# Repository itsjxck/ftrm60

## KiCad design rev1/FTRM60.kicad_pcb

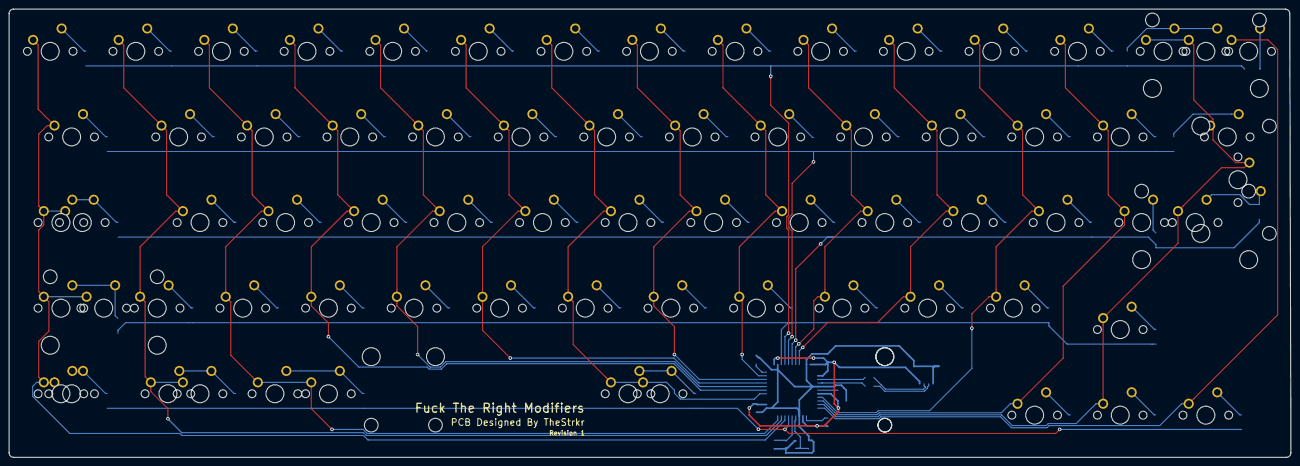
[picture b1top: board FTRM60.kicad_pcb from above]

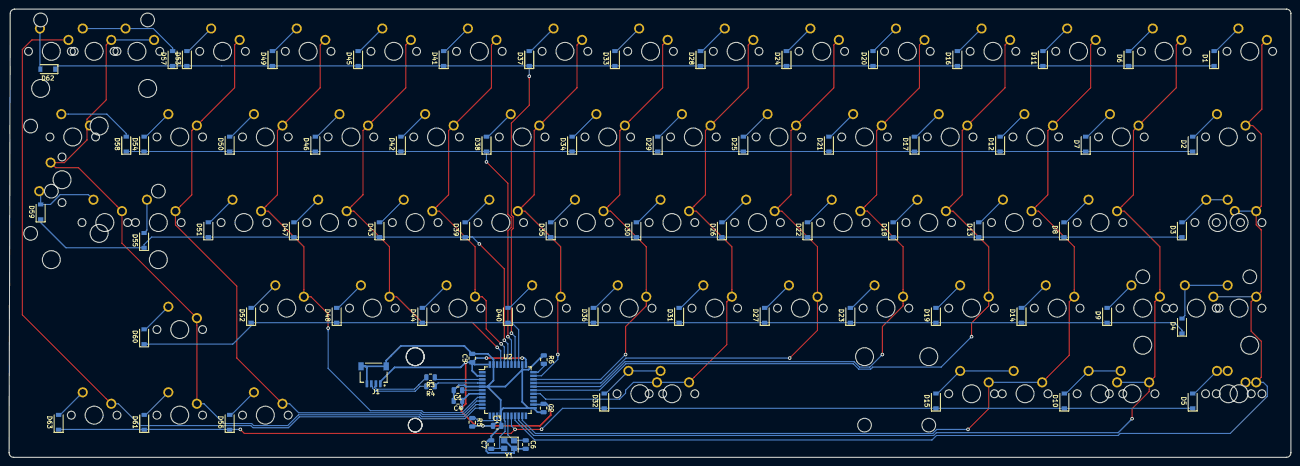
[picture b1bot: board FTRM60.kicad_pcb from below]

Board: 2 copper layers, 285.2 x 99.8 mm, 148 parts (77 on the bottom side), 94 nets.

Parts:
C1: 1uF; C_0805_2012Metric
C2, C3, C4: 0.1uF; C_0805_2012Metric
C5: 10uF; C_0805_2012Metric
C6, C7: 22pF; C_0805_2012Metric
D1, D2, D3, D4, D5, D6, D7, D8, D9, D10, D11, D12, D13, D14, D15, D16, D17, D18, D19, D20, D21, D22, D23, D24, D25, D26, D27, D28, D29, D30, D31, D32, D33, D34, D35, D36, D37, D38, D39, D40, D41, D42, D43, D44, D45, D46, D47, D48, D49, D50, D51, D52, D53, D54, D55, D56, D57, D58, D59, D60, D61, D62, D63: SOD-123; D_SOD-123
J1: SM04B-SRSS-TB(LF)(SN); JST_SM04B-SRSS-TB(LF)(SN)
MX1: K_ESC; MXOnly-1U-NoLED
MX2: K_TAB; MXOnly-1.5U-NoLED
MX3: K_CAPS_S; MXOnly-1.25U-NoLED
MX4: K_CAPS; MXOnly-1.75U-NoLED
MX5: K_LSHIFT_1.25U; MXOnly-1.25U-NoLED
MX6: K_LSHIFT_2.25U; MXOnly-2.25U-NoLED
MX7: K_LCTRL_1.25U; MXOnly-1.25U-NoLED
MX8: K_LCTRL_1.5U; MXOnly-1.5U-NoLED
MX9: K_1; MXOnly-1U-NoLED
MX10: K_Q; MXOnly-1U-NoLED
MX11: K_A; MXOnly-1U-NoLED
MX12: K_NUBS; MXOnly-1U-NoLED
MX13: K_LGUI_1.25U; MXOnly-1.25U-NoLED
MX14: K_LGUI_1.5U; MXOnly-1.5U-NoLED
MX15: K_2; MXOnly-1U-NoLED
MX16: K_W; MXOnly-1U-NoLED
MX17: K_S; MXOnly-1U-NoLED
MX18: K_Z; MXOnly-1U-NoLED
MX19: K_LALT_1.25U; MXOnly-1.25U-NoLED
MX20: K_LALT_1.5U; MXOnly-1.5U-NoLED
MX21: K_3; MXOnly-1U-NoLED
MX22: K_E; MXOnly-1U-NoLED
MX23: K_D; MXOnly-1U-NoLED
MX24: K_X; MXOnly-1U-NoLED
MX25: K_4; MXOnly-1U-NoLED
MX26: K_R; MXOnly-1U-NoLED
MX27: K_F; MXOnly-1U-NoLED
MX28: K_C; MXOnly-1U-NoLED
MX29: K_5; MXOnly-1U-NoLED
MX30: K_T; MXOnly-1U-NoLED
MX31: K_G; MXOnly-1U-NoLED
MX32: K_V; MXOnly-1U-NoLED
MX33: K_6; MXOnly-1U-NoLED
MX34: K_Y; MXOnly-1U-NoLED
MX35: K_H; MXOnly-1U-NoLED
MX36: K_B; MXOnly-1U-NoLED
MX37: K_SPC_7U; MXOnly-7U-ReversedStabilizers-NoLED
MX38: K_SPC_6.25U; MXOnly-6.25U-ReversedStabilizers-NoLED
MX39: K_7; MXOnly-1U-NoLED
MX40: K_U; MXOnly-1U-NoLED
MX41: K_J; MXOnly-1U-NoLED
MX42: K_N; MXOnly-1U-NoLED
MX43: K_8; MXOnly-1U-NoLED
MX44: K_I; MXOnly-1U-NoLED
MX45: K_K; MXOnly-1U-NoLED
MX46: K_M; MXOnly-1U-NoLED
MX47: K_9; MXOnly-1U-NoLED
MX48: K_O; MXOnly-1U-NoLED
MX49: K_L; MXOnly-1U-NoLED
MX50: K_COMM; MXOnly-1U-NoLED
MX51: K_0; MXOnly-1U-NoLED
MX52: K_P; MXOnly-1U-NoLED
MX53: K_SCLN; MXOnly-1U-NoLED
MX54: K_DOT; MXOnly-1U-NoLED
MX55: K_MINS; MXOnly-1U-NoLED
MX56: K_LBRC; MXOnly-1U-NoLED
MX57: K_QUOT; MXOnly-1U-NoLED
MX58: K_SLSH; MXOnly-1U-NoLED
MX59: K_EQL; MXOnly-1U-NoLED
MX60: K_RBRC; MXOnly-1U-NoLED
MX61: K_NUHS; MXOnly-1U-NoLED
MX62: K_LEFT; MXOnly-1U-NoLED
MX63: K_BSPC_S1; MXOnly-1U-NoLED
MX64: K_BSPC; MXOnly-2U-NoLED
MX65: K_BSLS; MXOnly-1.5U-NoLED
MX66: K_ENT_ANSI; MXOnly-2.25U-NoLED
MX67: K_ENT_ISO; MXOnly-ISO-ROTATED-ReversedStabilizers-NoLED
MX68: K_UP; MXOnly-1U-NoLED
MX69: K_DOWN; MXOnly-1U-NoLED
MX70: K_BSPC_S2; MXOnly-1U-NoLED
MX71: K_RIGHT; MXOnly-1U-NoLED
R3, R4: 22; R_0805_2012Metric
R5, R6: 10k; R_0805_2012Metric
U2: ATmega32U4-AU; TQFP-44_10x10mm_P0.8mm
Y1: 16MHz; Crystal_SMD_3225-4Pin_3.2x2.5mm

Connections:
+5V: C2.1, C3.1, C4.1, C5.1, J1.1, R5.2, U2.2, U2.7, U2.14, U2.24, U2.34, U2.44
/COL0: MX1.1, MX2.1, MX3.1, MX4.1, MX5.1, MX6.1, MX7.1, MX8.1, U2.19
/COL1: MX9.1, MX10.1, MX11.1, MX12.1, MX13.1, MX14.1, U2.20
/COL2: MX15.1, MX16.1, MX17.1, MX18.1, MX19.1, MX20.1, U2.21
/COL3: MX21.1, MX22.1, MX23.1, MX24.1, U2.28
/COL4: MX25.1, MX26.1, MX27.1, MX28.1, U2.29
/COL5: MX29.1, MX30.1, MX31.1, MX32.1, U2.30
/COL6: MX33.1, MX34.1, MX35.1, MX36.1, MX37.1, MX38.1, U2.27
/COL7: MX39.1, MX40.1, MX41.1, MX42.1, U2.31
/COL8: MX43.1, MX44.1, MX45.1, MX46.1, U2.32
/COL9: MX47.1, MX48.1, MX49.1, MX50.1, U2.40
/COL10: MX51.1, MX52.1, MX53.1, MX54.1, U2.41
/COL11: MX55.1, MX56.1, MX57.1, MX58.1, U2.8
/COL12: MX59.1, MX60.1, MX61.1, MX62.1, U2.9
/COL13: MX63.1, MX64.1, MX65.1, MX66.1, MX67.1, MX68.1, MX69.1, U2.10
/COL14: MX70.1, MX71.1, U2.11
/ROW0: D1.1, D6.1, D11.1, D16.1, D20.1, D24.1, D28.1, D33.1, D37.1, D41.1, D45.1, D49.1, D53.1, D57.1, D62.1, U2.37
/ROW1: D2.1, D7.1, D12.1, D17.1, D21.1, D25.1, D29.1, D34.1, D38.1, D42.1, D46.1, D50.1, D54.1, D58.1, U2.38
/ROW2: D3.1, D8.1, D13.1, D18.1, D22.1, D26.1, D30.1, D35.1, D39.1, D43.1, D47.1, D51.1, D55.1, D59.1, U2.39
/ROW3: D4.1, D9.1, D14.1, D19.1, D23.1, D27.1, D31.1, D36.1, D40.1, D44.1, D48.1, D52.1, D60.1, U2.36
/ROW4: D5.1, D10.1, D15.1, D32.1, D56.1, D61.1, D63.1, U2.18
D+: J1.3, R4.2
D-: J1.2, R3.2
GND: C1.2, C2.2, C3.2, C4.2, C5.2, C6.2, C7.2, J1.4, J1.S1, J1.S2, R6.1, U2.5, U2.15, U2.23, U2.35, U2.43, Y1.2, Y1.4
unnamed: C1.1, U2.6
unnamed: D1.2, MX1.2
unnamed: D2.2, MX2.2
unnamed: D3.2, MX3.2, MX4.2
unnamed: D4.2, MX5.2, MX6.2
unnamed: D5.2, MX7.2, MX8.2
unnamed: D6.2, MX9.2
unnamed: D7.2, MX10.2
unnamed: D8.2, MX11.2
unnamed: D9.2, MX12.2
unnamed: D10.2, MX13.2, MX14.2
unnamed: D11.2, MX15.2
unnamed: D12.2, MX16.2
unnamed: D13.2, MX17.2
unnamed: D14.2, MX18.2
unnamed: D15.2, MX19.2, MX20.2
unnamed: D16.2, MX21.2
unnamed: D17.2, MX22.2
unnamed: D18.2, MX23.2
unnamed: D19.2, MX24.2
unnamed: D20.2, MX25.2
unnamed: D21.2, MX26.2
unnamed: D22.2, MX27.2
unnamed: D23.2, MX28.2
unnamed: D24.2, MX29.2
unnamed: D25.2, MX30.2
unnamed: D26.2, MX31.2
unnamed: D27.2, MX32.2
unnamed: D28.2, MX33.2
unnamed: D29.2, MX34.2
unnamed: D30.2, MX35.2
unnamed: D31.2, MX36.2
unnamed: D32.2, MX37.2, MX38.2
unnamed: D33.2, MX39.2
unnamed: D34.2, MX40.2
unnamed: D35.2, MX41.2
unnamed: D36.2, MX42.2
unnamed: D37.2, MX43.2
unnamed: D38.2, MX44.2
unnamed: D39.2, MX45.2
unnamed: D40.2, MX46.2
unnamed: D41.2, MX47.2
unnamed: D42.2, MX48.2
unnamed: D43.2, MX49.2
unnamed: D44.2, MX50.2
unnamed: D45.2, MX51.2
unnamed: D46.2, MX52.2
unnamed: D47.2, MX53.2
unnamed: D48.2, MX54.2
unnamed: D49.2, MX55.2
unnamed: D50.2, MX56.2
unnamed: D51.2, MX57.2
unnamed: D52.2, MX58.2
unnamed: D53.2, MX59.2
unnamed: D54.2, MX60.2
unnamed: D55.2, MX61.2
unnamed: D56.2, MX62.2
unnamed: D57.2, MX63.2, MX64.2
unnamed: D58.2, MX65.2
unnamed: D59.2, MX66.2, MX67.2
unnamed: D60.2, MX68.2
unnamed: D61.2, MX69.2
unnamed: D62.2, MX70.2
unnamed: D63.2, MX71.2
unnamed: R3.1, U2.3
unnamed: R4.1, U2.4
unnamed: R5.1, U2.13
unnamed: R6.2, U2.33
XTAL1: C6.1, U2.17, Y1.1
XTAL2: C7.1, U2.16, Y1.3

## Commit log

2020-04-13 Initial
2020-10-03 Some late updates
